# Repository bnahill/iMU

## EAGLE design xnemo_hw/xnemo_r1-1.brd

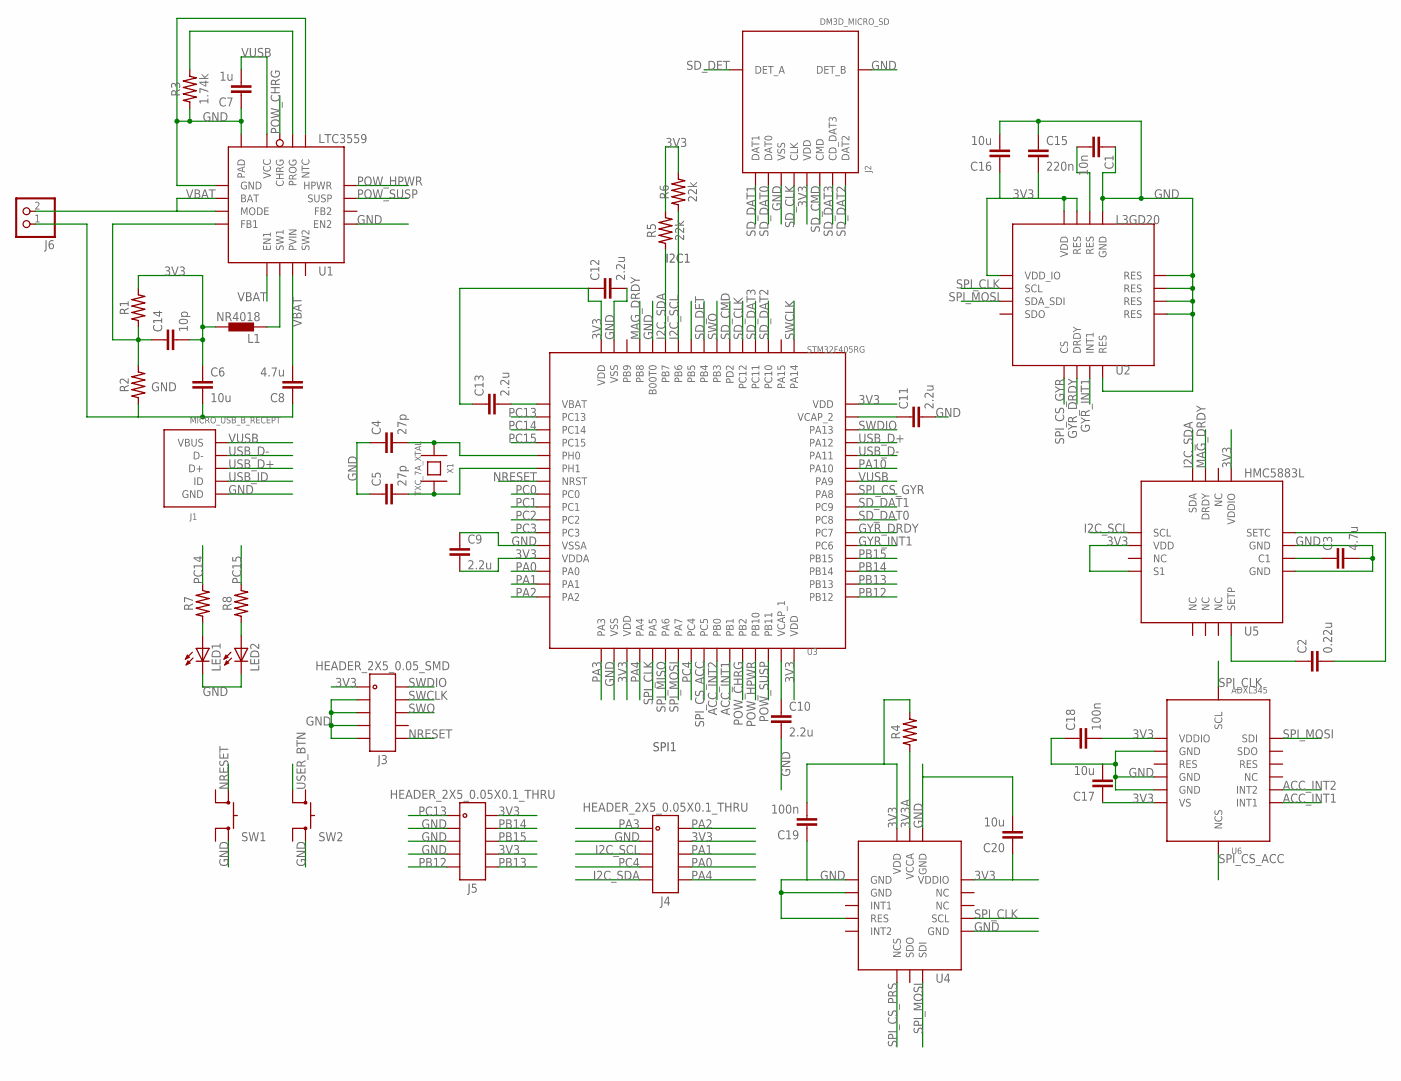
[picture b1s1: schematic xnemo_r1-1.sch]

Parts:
C1: 10n; C0402
C2: 0.22u; C0402
C3, C8: 4.7u; C0805
C4, C5: 27p; C0402
C6, C16, C17, C20: 10u; C0805
C7: 1u; C0603
C9, C10, C11, C12, C13: 2.2u; C0603
C14: 10p; C0402
C15: 220n; C0402
C18, C19: 100n; C0402
J1: MICRO_USB_B_RECEPT; FCI_MICRO_USB_B
J2: DM3D_MICRO_SD; HIROSE_DM3D
J3: HEADER_2X5_0.05_SMD
J4, J5: HEADER_2X5_0.05X0.1_THRU
J6: PINHD-1X2; 1X02
L1: NR4018; L_401X
LED1, LED2: LEDCHIPLED_0603; CHIPLED_0603
R1, R2, R7, R8: RESISTOR-0402; SMD0402
R3: 1.74k; SMD0402
R4: RESISTOR-0603; SMD0603
R5, R6: 22k; SMD0402
SW1, SW2: ALPS_SKQG
U1: LTC3559; LT_QFN16_3X3
U2: L3GD20; ST_LGA16_4X4
U3: STM32F405RG; ST_LQFP64
U4: LPS331AP; ST_HCLGA-16L
U5: HMC5883L; HW_LCC16_3X3
U6: ADXL345; AD_LGA14_3X5
X1: TXC_7A_XTAL

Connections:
3V3: C6.1, C9.2, C12.1, C13.1, C14.2, C15.2, C16.1, C17.1, C18.2, C19.2, C20.1, J2.P$5 (VDD), J3.1, J4.4, J5.2, J5.8, L1.P$2 (2), R1.P$1, R4.P$1, R5.P$1, R6.P$1, U2.P$1 (VDD_IO), U2.P$15 (RES), U2.P$16 (VDD), U3.P$13 (VDDA), U3.P$19 (VDD), U3.P$32 (VDD), U3.P$48 (VDD), U3.P$64 (VDD), U4.P$1 (VDDIO), U4.P$14 (VDD), U5.P$2 (VDD), U5.P$4 (S1), U5.P$13 (VDDIO), U6.P$1 (VDDIO), U6.P$6 (VS)
3V3A: R4.P$2, U4.P$15 (VCCA)
ACC_INT1: U3.P$27 (PB1), U6.P$8 (INT1)
ACC_INT2: U3.P$26 (PB0), U6.P$9 (INT2)
BUCK_FB1: C14.1, R1.P$2, R2.P$1, U1.P$4 (FB1)
BUCK_SW1: L1.P$1 (1), U1.P$6 (SW1)
GND: C1.1, C3.2, C4.1, C5.1, C6.2, C7.1, C8.1, C9.1, C10.2, C11.2, C12.2, C15.1, C16.2, C17.2, C18.1, C19.1, C20.2, J1.P$5 (GND), J2.P$3 (VSS), J2.P$9 (DET_B), J3.3, J3.5, J3.7, J3.9, J4.3, J5.3, J5.5, J5.7, J6.1, LED1.C, LED2.C, R2.P$2, R3.P$2, SW1.2_2 (2), SW2.2_2 (2), U1.P$1 (GND), U1.P$9 (EN2), U1.P$13 (NTC), U1.P$17 (PAD), U2.P$8 (RES), U2.P$9 (RES), U2.P$10 (RES), U2.P$11 (RES), U2.P$12 (RES), U2.P$13 (GND), U3.P$12 (VSSA), U3.P$18 (VSS), U3.P$60 (B00T0), U3.P$63 (VSS), U4.P$5 (GND), U4.P$10 (RES), U4.P$12 (GND), U4.P$13 (GND), U4.P$16 (GND), U5.P$9 (GND), U5.P$11 (GND), U6.P$2 (GND), U6.P$4 (GND), U6.P$5 (GND)
GYR_DRDY: U2.P$6 (DRDY), U3.P$38 (PC7)
GYR_INT1: U2.P$7 (INT1), U3.P$37 (PC6)
GYR_RES: C1.2, U2.P$14 (RES)
I2C_SCL: J4.5, R6.P$2, U3.P$58 (PB6), U5.P$1 (SCL)
I2C_SDA: J4.9, R5.P$2, U3.P$59 (PB7), U5.P$16 (SDA)
MAG_C1: C3.1, U5.P$10 (C1)
MAG_DRDY: U3.P$61 (PB8), U5.P$15 (DRDY)
MAG_SETC: C2.2, U5.P$12 (SETC)
MAG_SETP: C2.1, U5.P$8 (SETP)
unnamed: LED1.A, R7.P$2
unnamed: LED2.A, R8.P$2
NRESET: J3.10, SW1.1_2 (1), U3.P$7 (NRST)
OSC_IN: C4.2, U3.P$5 (PH0), X1.P$2
OSC_OUT: C5.2, U3.P$6 (PH1), X1.P$1
PA0: J4.8, U3.P$14 (PA0)
PA1: J4.6, U3.P$15 (PA1)
PA2: J4.2, U3.P$16 (PA2)
PA3: J4.1, U3.P$17 (PA3)
PA4: J4.10, U3.P$20 (PA4)
PA10: U3.P$43 (PA10)
PB12: J5.9, U3.P$33 (PB12)
PB13: J5.10, U3.P$34 (PB13)
PB14: J5.4, U3.P$35 (PB14)
PB15: J5.6, U3.P$36 (PB15)
PC0: U3.P$8 (PC0)
PC1: U3.P$9 (PC1)
PC2: U3.P$10 (PC2)
PC3: U3.P$11 (PC3)
PC4: J4.7, U3.P$24 (PC4)
PC13: J5.1, U3.P$2 (PC13)
PC14: R7.P$1, U3.P$3 (PC14)
PC15: R8.P$1, U3.P$4 (PC15)
POW_CHRG: U1.P$15 (CHRG), U3.P$28 (PB2)
POW_HPWR: U1.P$12 (HPWR), U3.P$29 (PB10)
POW_PROG: R3.P$1, U1.P$14 (PROG)
POW_SUSP: U1.P$11 (SUSP), U3.P$30 (PB11)
SD_CLK: J2.P$4 (CLK), U3.P$53 (PC12)
SD_CMD: J2.P$6 (CMD), U3.P$54 (PD2)
SD_DAT0: J2.P$2 (DAT0), U3.P$39 (PC8)
SD_DAT1: J2.P$1 (DAT1), U3.P$40 (PC9)
SD_DAT2: J2.P$8 (DAT2), U3.P$51 (PC10)
SD_DAT3: J2.P$7 (CD_DAT3), U3.P$52 (PC11)
SD_DET: J2.P$10 (DET_A), U3.P$56 (PB4)
SPI_CLK: U2.P$2 (SCL), U3.P$21 (PA5), U4.P$4 (SCL), U6.P$14 (SCL)
SPI_CS_ACC: U3.P$25 (PC5), U6.P$7 (NCS)
SPI_CS_GYR: U2.P$5 (CS), U3.P$41 (PA8)
SPI_CS_PRS: U4.P$8 (NCS)
SPI_MISO: U3.P$22 (PA6)
SPI_MOSI: U2.P$3 (SDA_SDI), U3.P$23 (PA7), U4.P$6 (SDI), U6.P$13 (SDI)
SWCLK: J3.4, U3.P$49 (PA14)
SWDIO: J3.2, U3.P$46 (PA13)
SWO: J3.6, U3.P$55 (PB3)
UC_VBAT: C13.2, U3.P$1 (VBAT)
USB_D+: J1.P$3 (D+), U3.P$45 (PA12)
USB_D-: J1.P$2 (D-), U3.P$44 (PA11)
USB_ID: J1.P$4 (ID)
USER_BTN: SW2.1_1 (1), U3.P$57 (PB5)
VBAT: C8.2, J6.2, U1.P$2 (BAT), U1.P$3 (MODE), U1.P$5 (EN1), U1.P$7 (PVIN)
VCAP_1: C10.1, U3.P$31 (VCAP_1)
VCAP_2: C11.1, U3.P$47 (VCAP_2)
VUSB: C7.2, J1.P$1 (VBUS), U1.P$16 (VCC), U3.P$42 (PA9)

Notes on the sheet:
SPI1
I2C1

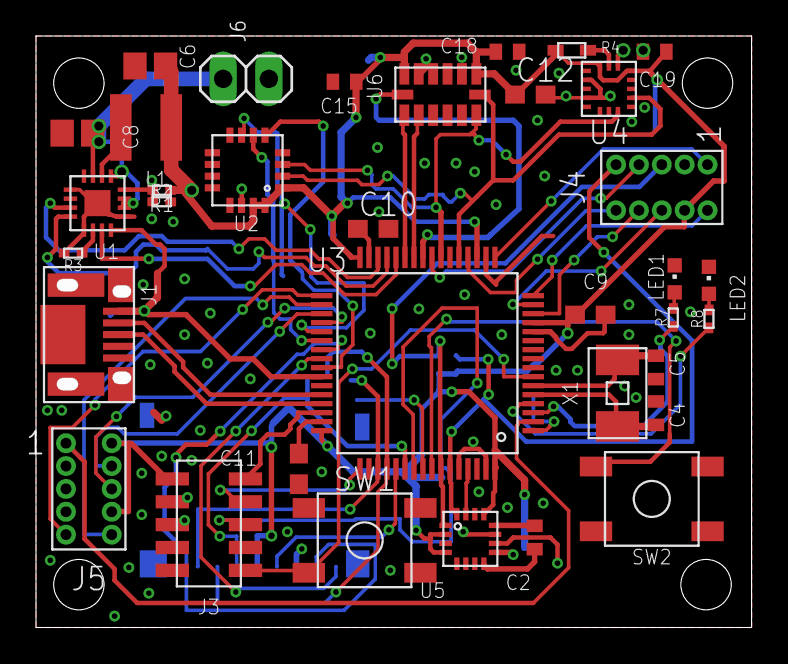
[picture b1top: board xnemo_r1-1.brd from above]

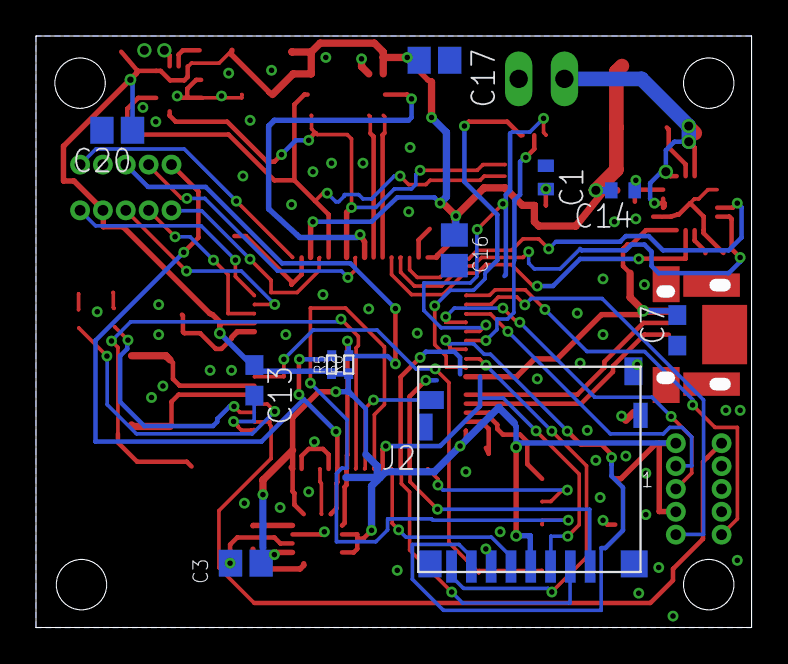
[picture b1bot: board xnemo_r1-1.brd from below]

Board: 2 copper layers, 39.1 x 32.2 mm, 46 parts (11 on the bottom side), 60 nets.

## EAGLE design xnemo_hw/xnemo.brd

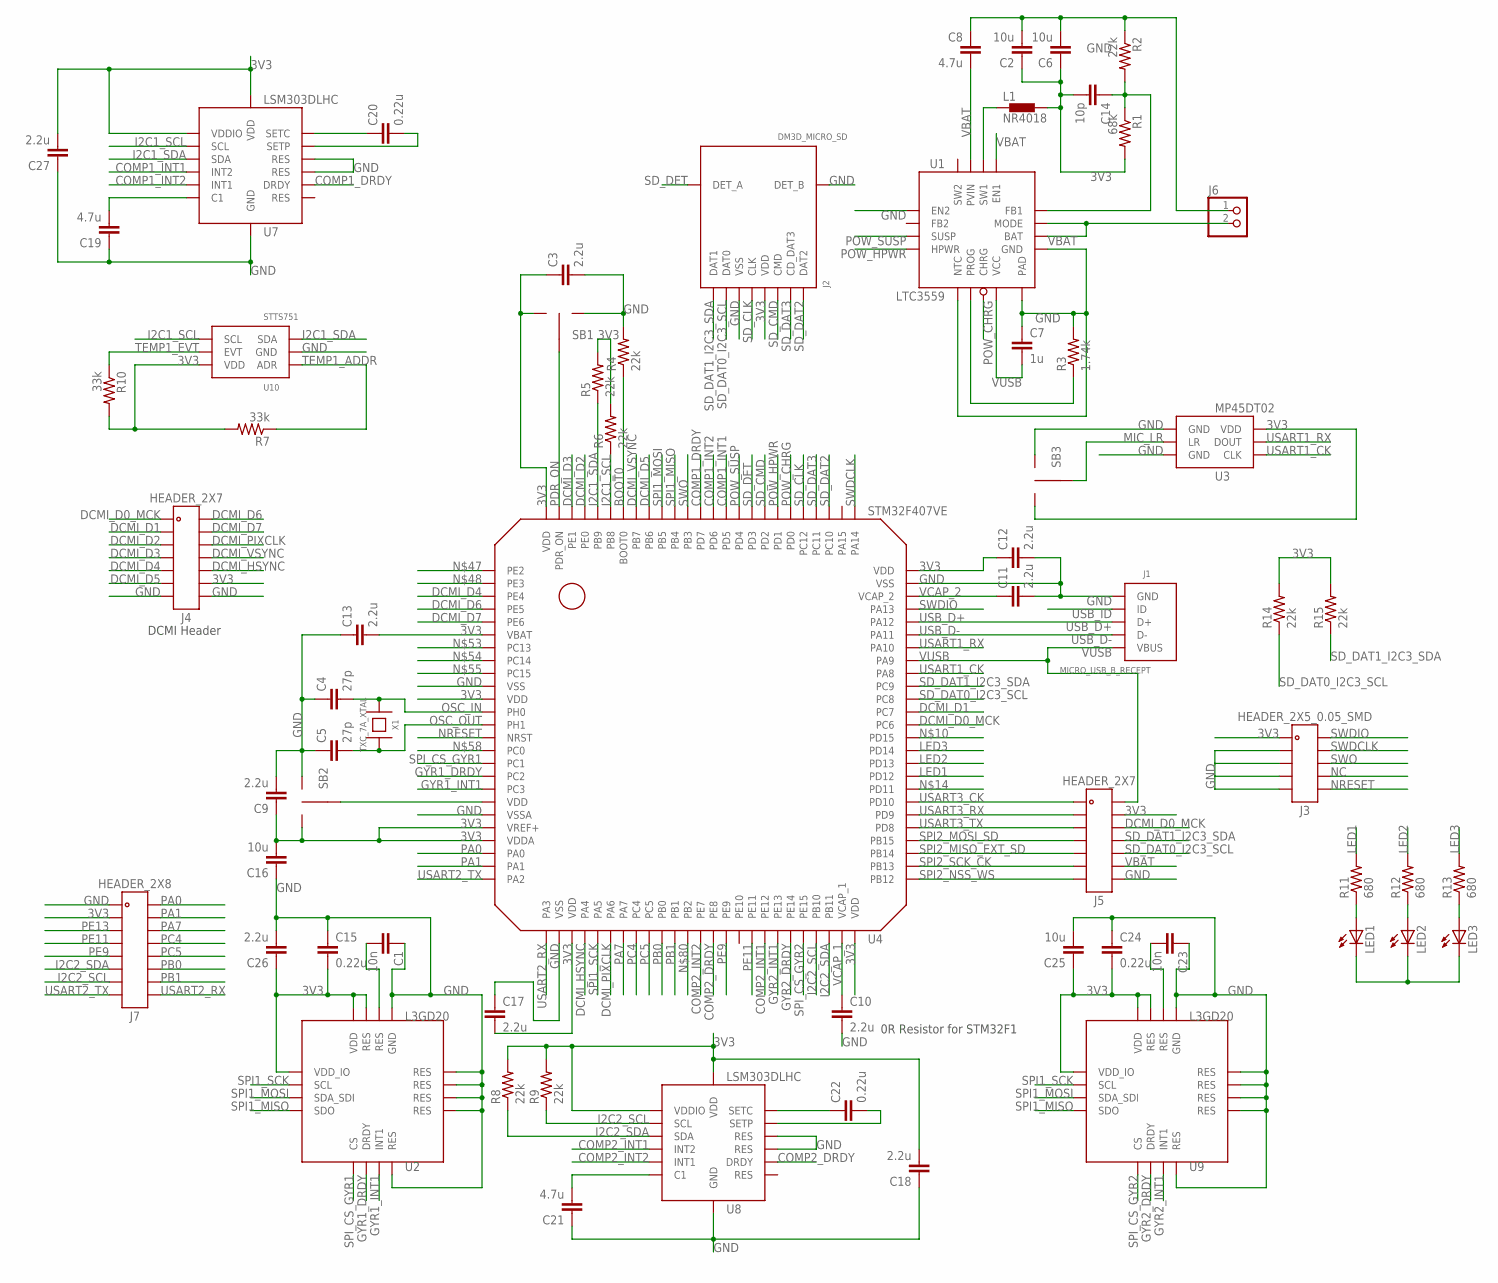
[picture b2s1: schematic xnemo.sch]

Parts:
C1, C23: 10n; C0402
C2, C6, C16, C25: 10u; C0805
C3, C9, C10, C11, C12, C13, C17, C18, C26, C27: 2.2u; C0603
C4, C5: 27p; C0402
C7: 1u; C0603
C8, C19, C21: 4.7u; C0805
C14: 10p; C0402
C15, C20, C22, C24: 0.22u; C0402
J1: MICRO_USB_B_RECEPT; FCI_MICRO_USB_B
J2: DM3D_MICRO_SD; HIROSE_DM3D
J3: HEADER_2X5_0.05_SMD
J4, J5: HEADER_2X7; HEADER_2X7_0.05X0.1_THRU
J6: PINHD-1X2; 1X02
J7: HEADER_2X8; HEADER_2X8_0.05X0.1_THRU
L1: NR4018; L_401X
LED1, LED2, LED3: LEDSML0805; SML0805
R1: 68k; R0402
R2, R4, R5, R6, R8, R9, R14, R15: 22k; R0402
R3: 1.74k; R0402
R7, R10: 33k; R0402
R11, R12, R13: 680; R0402
SB1, SB2, SB3: SOLDER_BRIDGE_2
U1: LTC3559; LT_QFN16_3X3
U2, U9: L3GD20; ST_LGA16_4X4
U3: MP45DT02; ST_HLGA6
U4: STM32F407VE; ST_LQFP100
U7, U8: LSM303DLHC; ST_LGA14_3X5
U10: STTS751; ST_UDFN-6L_2X2
X1: TXC_7A_XTAL

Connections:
3V3: C2.1, C3.1, C6.1, C9.1, C12.1, C13.2, C14.2, C15.2, C16.2, C17.2, C18.2, C24.2, C25.1, C26.1, C27.2, J2.P$5 (VDD), J3.1, J4.12, J5.4, J7.3, L1.P$2 (2), R1.2, R5.2, R6.2, R7.2, R8.2, R9.2, R10.2, R14.2, R15.2, SB1.P$1, SB2.P$1, SB3.P$1, U2.P$1 (VDD_IO), U2.P$15 (RES), U2.P$16 (VDD), U3.6 (VDD), U4.P$6 (VBAT), U4.P$11 (VDD), U4.P$21 (VREF+), U4.P$22 (VDDA), U4.P$28 (VDD), U4.P$50 (VDD), U4.P$75 (VDD), U4.P$100 (VDD), U7.P$1 (VDDIO), U7.P$14 (VDD), U8.P$1 (VDDIO), U8.P$14 (VDD), U9.P$1 (VDD_IO), U9.P$15 (RES), U9.P$16 (VDD), U10.3 (VDD)
BOOT0: R4.1, U4.P$94 (BOOT0)
BUCK_FB1: C14.1, R1.1, R2.2, U1.P$4 (FB1)
BUCK_SW1: L1.P$1 (1), U1.P$6 (SW1)
COMP1_C1: C19.2, U7.P$6 (C1)
COMP1_DRDY: U4.P$88 (PD7), U7.P$9 (DRDY)
COMP1_INT1: U4.P$86 (PD5), U7.P$4 (INT2)
COMP1_INT2: U4.P$87 (PD6), U7.P$5 (INT1)
COMP2_C1: C21.2, U8.P$6 (C1)
COMP2_DRDY: U4.P$39 (PE8), U8.P$9 (DRDY)
COMP2_INT1: U4.P$43 (PE12), U8.P$4 (INT2)
COMP2_INT2: U4.P$38 (PE7), U8.P$5 (INT1)
DCMI_D0_MCK: J4.1, J5.6, U4.P$63 (PC6)
DCMI_D1: J4.3, U4.P$64 (PC7)
DCMI_D2: J4.5, U4.P$97 (PE0)
DCMI_D3: J4.7, U4.P$98 (PE1)
DCMI_D4: J4.9, U4.P$3 (PE4)
DCMI_D5: J4.11, U4.P$92 (PB6)
DCMI_D6: J4.2, U4.P$4 (PE5)
DCMI_D7: J4.4, U4.P$5 (PE6)
DCMI_HSYNC: J4.10, U4.P$29 (PA4)
DCMI_PIXCLK: J4.6, U4.P$31 (PA6)
DCMI_VSYNC: J4.8, U4.P$93 (PB7)
GND: C1.1, C2.2, C3.2, C4.1, C5.1, C6.2, C7.1, C8.1, C9.2, C10.2, C11.2, C12.2, C13.1, C15.1, C16.1, C17.1, C18.1, C19.1, C21.1, C23.1, C24.1, C25.2, C26.2, C27.1, J1.P$5 (GND), J2.P$3 (VSS), J2.P$9 (DET_B), J3.3, J3.5, J3.7, J3.9, J4.13, J4.14, J5.14, J6.1, J7.1, LED1.C, LED2.C, LED3.C, R2.1, R3.2, R4.2, SB1.P$3, SB2.P$3, SB3.P$3, U1.P$1 (GND), U1.P$9 (EN2), U1.P$13 (NTC), U1.P$17 (PAD), U2.P$8 (RES), U2.P$9 (RES), U2.P$10 (RES), U2.P$11 (RES), U2.P$12 (RES), U2.P$13 (GND), U3.1 (GND), U3.3 (GND), U4.P$10 (VSS), U4.P$20 (VSSA), U4.P$27 (VSS), U4.P$74 (VSS), U7.P$7 (GND), U7.P$10 (RES), U7.P$11 (RES), U8.P$7 (GND), U8.P$10 (RES), U8.P$11 (RES), U9.P$8 (RES), U9.P$9 (RES), U9.P$10 (RES), U9.P$11 (RES), U9.P$12 (RES), U9.P$13 (GND), U10.5 (GND)
GYR1_DRDY: U2.P$6 (DRDY), U4.P$17 (PC2)
GYR1_INT1: U2.P$7 (INT1), U4.P$18 (PC3)
GYR2_DRDY: U4.P$45 (PE14), U9.P$6 (DRDY)
GYR2_INT1: U4.P$44 (PE13), U9.P$7 (INT1)
GYR_RES1: C1.2, U2.P$14 (RES)
GYR_RES2: C23.2, U9.P$14 (RES)
I2C1_SCL: R6.1, U4.P$95 (PB8), U7.P$2 (SCL), U10.1 (SCL)
I2C1_SDA: R5.1, U4.P$96 (PB9), U7.P$3 (SDA), U10.6 (SDA)
I2C2_SCL: J7.13, R9.1, U4.P$47 (PB10), U8.P$2 (SCL)
I2C2_SDA: J7.11, R8.1, U4.P$48 (PB11), U8.P$3 (SDA)
LED1: R11.2, U4.P$59 (PD12)
LED2: R12.2, U4.P$60 (PD13)
LED3: R13.2, U4.P$61 (PD14)
MIC_LR: SB3.P$2, U3.2 (LR)
unnamed: C22.2, U8.P$12 (SETP)
unnamed: C20.2, U7.P$12 (SETP)
unnamed: LED1.A, R11.1
unnamed: LED2.A, R12.1
unnamed: LED3.A, R13.1
unnamed: C22.1, U8.P$13 (SETC)
unnamed: C20.1, U7.P$13 (SETC)
unnamed: SB2.P$2, U4.P$19 (VDD)
NC: J3.8
NRESET: J3.10, U4.P$14 (NRST)
OSC_IN: C4.2, U4.P$12 (PH0), X1.P$2
OSC_OUT: C5.2, U4.P$13 (PH1), X1.P$1
PA0: J7.2, U4.P$23 (PA0)
PA1: J7.4, U4.P$24 (PA1)
PA7: J7.6, U4.P$32 (PA7)
PB0: J7.12, U4.P$35 (PB0)
PB1: J7.14, U4.P$36 (PB1)
PC4: J7.8, U4.P$33 (PC4)
PC5: J7.10, U4.P$34 (PC5)
PDR_ON: SB1.P$2, U4.P$99 (PDR_ON)
PE9: J7.9, U4.P$40 (PE9)
PE11: J7.7, U4.P$42 (PE11)
PE13: J7.5
POW_CHRG: U1.P$15 (CHRG), U4.P$81 (PD0)
POW_HPWR: U1.P$12 (HPWR), U4.P$82 (PD1)
POW_PROG: R3.1, U1.P$14 (PROG)
POW_SUSP: U1.P$11 (SUSP), U4.P$85 (PD4)
SD_CLK: J2.P$4 (CLK), U4.P$80 (PC12)
SD_CMD: J2.P$6 (CMD), U4.P$83 (PD2)
SD_DAT0_I2C3_SCL: J2.P$2 (DAT0), J5.10, R14.1, U4.P$65 (PC8)
SD_DAT1_I2C3_SDA: J2.P$1 (DAT1), J5.8, R15.1, U4.P$66 (PC9)
SD_DAT2: J2.P$8 (DAT2), U4.P$78 (PC10)
SD_DAT3: J2.P$7 (CD_DAT3), U4.P$79 (PC11)
SD_DET: J2.P$10 (DET_A), U4.P$84 (PD3)
SPI1_MISO: U2.P$4 (SDO), U4.P$90 (PB4), U9.P$4 (SDO)
SPI1_MOSI: U2.P$3 (SDA_SDI), U4.P$91 (PB5), U9.P$3 (SDA_SDI)
SPI1_SCK: U2.P$2 (SCL), U4.P$30 (PA5), U9.P$2 (SCL)
SPI2_MISO_EXT_SD: J5.9, U4.P$53 (PB14)
SPI2_MOSI_SD: J5.7, U4.P$54 (PB15)
SPI2_NSS_WS: J5.13, U4.P$51 (PB12)
SPI2_SCK_CK: J5.11, U4.P$52 (PB13)
SPI_CS_GYR1: U2.P$5 (CS), U4.P$16 (PC1)
SPI_CS_GYR2: U4.P$46 (PE15), U9.P$5 (CS)
SWDCLK: J3.4, U4.P$76 (PA14)
SWDIO: J3.2, U4.P$72 (PA13)
SWO: J3.6, U4.P$89 (PB3)
TEMP1_ADDR: R7.1, U10.4 (ADR)
TEMP1_EVT: R10.1, U10.2 (EVT)
USART1_CK: U3.4 (CLK), U4.P$67 (PA8)
USART1_RX: U3.5 (DOUT), U4.P$69 (PA10)
USART2_RX: J7.16, U4.P$26 (PA3)
USART2_TX: J7.15, U4.P$25 (PA2)
USART3_CK: J5.1, U4.P$57 (PD10)
USART3_RX: J5.3, U4.P$56 (PD9)
USART3_TX: J5.5, U4.P$55 (PD8)
USB_D+: J1.P$3 (D+), U4.P$71 (PA12)
USB_D-: J1.P$2 (D-), U4.P$70 (PA11)
USB_ID: J1.P$4 (ID)
VBAT: C8.2, J5.12, J6.2, U1.P$2 (BAT), U1.P$3 (MODE), U1.P$5 (EN1), U1.P$7 (PVIN)
VCAP_1: C10.1, U4.P$49 (VCAP_1)
VCAP_2: C11.1, U4.P$73 (VCAP_2)
VUSB: C7.2, J1.P$1 (VBUS), J5.2, U1.P$16 (VCC), U4.P$68 (PA9)

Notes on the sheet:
0R Resistor for STM32F1
DCMI Header

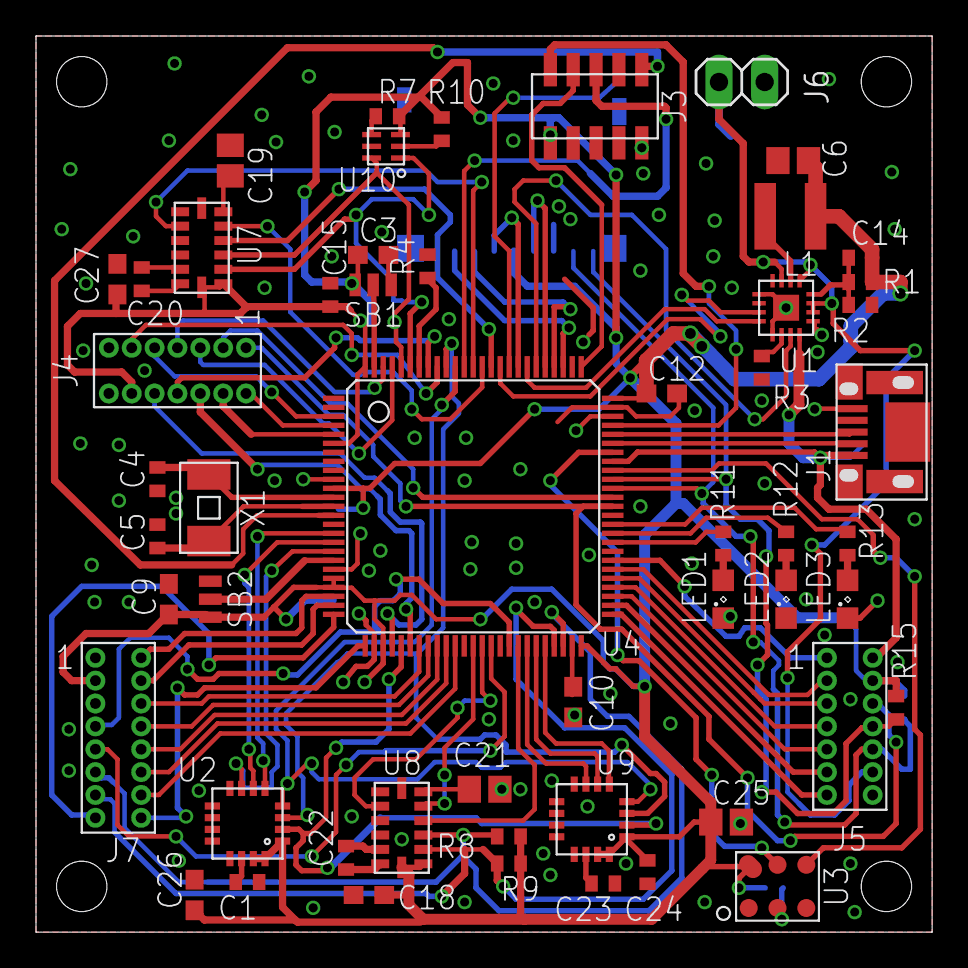
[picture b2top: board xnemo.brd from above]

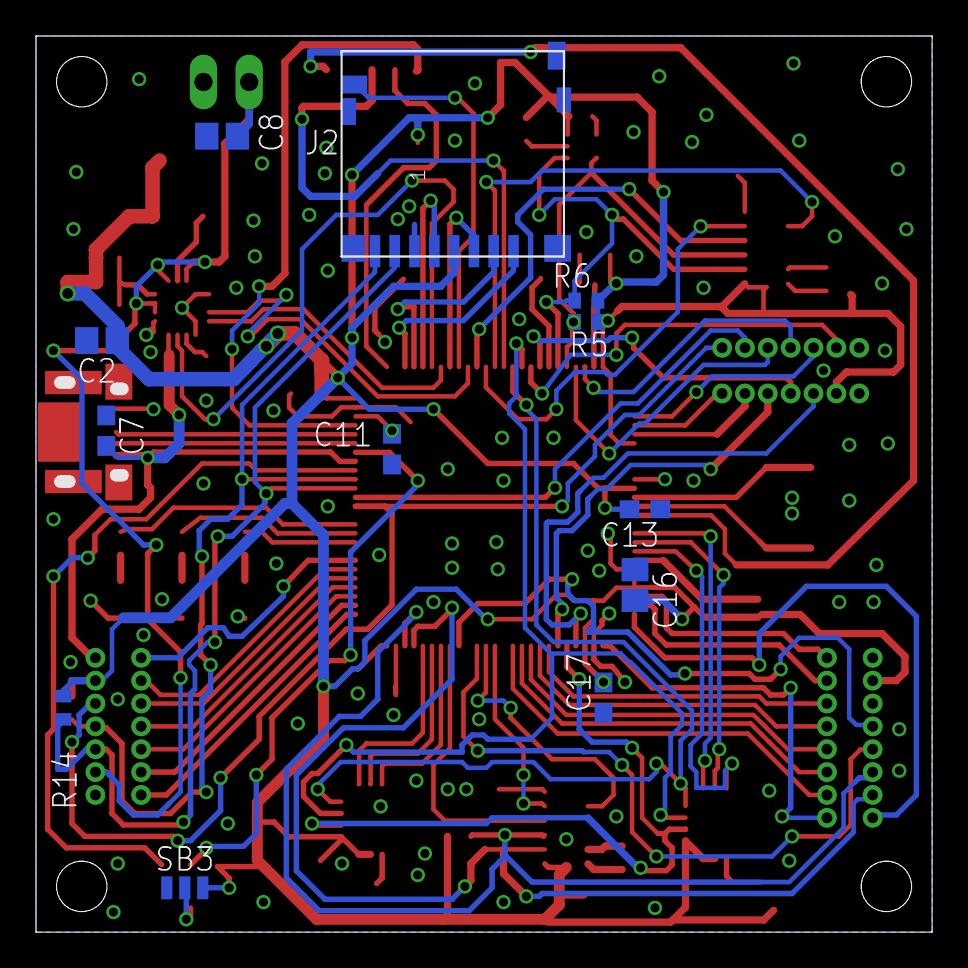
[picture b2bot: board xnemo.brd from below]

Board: 2 copper layers, 49.1 x 49.1 mm, 65 parts (12 on the bottom side), 97 nets.

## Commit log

2011-12-07 Initial commit with datasheets
2011-12-07 Added reference manual for stm32f4
2011-12-08 Added basic schematic which contains most of the parts.
2012-01-06 Added eagle stuff and changed gyros and charger
2012-01-07 Updated schematic to all essential connections, started board to make smarter pin selections by including routing considerations
2012-01-08 Updated some little things and added JTAG header
2012-01-09 Started bord
2012-01-11 Most of the PCB is routed
2012-01-11 Mostly routed!
2012-01-12 Passes DRC
2012-01-12 Expansion headers are now thru-hole
2012-01-14 r1 submitted
2012-03-08 Started conversion to larger PCB using LQFP100
2012-03-08 More junk added -- 2 compass units...
2012-03-12 Started routing
2012-03-15 Added datasheet, fixed some footprints
2012-03-15 All connections made -- no DRC yet
2012-03-15 Added microphone, DRC passed, no airwires
2012-03-15 Added microphone datasheet
2012-03-16 Attempting to genereate CAM files
2012-03-16 Fixed missing connection
2012-03-19 Moved some text on board, generated gerbers
2012-04-07 Removed old KiCAD stuff
2012-04-13 Updated USB connector footprint
2012-04-16 Added some software stuffs
2012-04-16 Added support for non-DMA SPI transfers
2012-04-24 Gyro works for both DMA and regular SPI
2012-04-30 Added I2C support
2012-05-11 All sorts of fun trying to get I2C1 working
2012-05-14 More I2C code to test (reading)
2012-05-15 Made I2C stuff work
2012-05-15 All IMU components work!
2012-05-17 Added generic SPI master library, modified L3GD20 to use it.
2012-05-17 New SPI driver works
2012-05-21 Small adjustment in I2C
2012-05-21 Added SDIO support
2012-05-26 Cleaned up sensor drivers
2012-05-27 Added USB sources
2012-05-27 Added GDB script for KDevelop debugging
2012-05-27 Added USB sources to CMakeLists
2012-05-29 Changed some names on the gyroscope
2012-05-29 Fixed a scaling issue with the accelerometers
2012-05-29 Enable second LSM303 and L3GD20
2012-05-29 Added extension of the old r1 board
2012-06-15 Fixing up R1 schematic for R1A
2012-06-17 Added pressure sensor datasheet
2012-07-16 I don't remember
2012-07-19 Routed, now to touch up r1.1
2012-09-02 Added additional hardware abstraction to support multiple platform configurations
2012-10-13 Start moving everything over to C++
2012-11-14 Built out C++ I2C driver and started MMA8452Q
